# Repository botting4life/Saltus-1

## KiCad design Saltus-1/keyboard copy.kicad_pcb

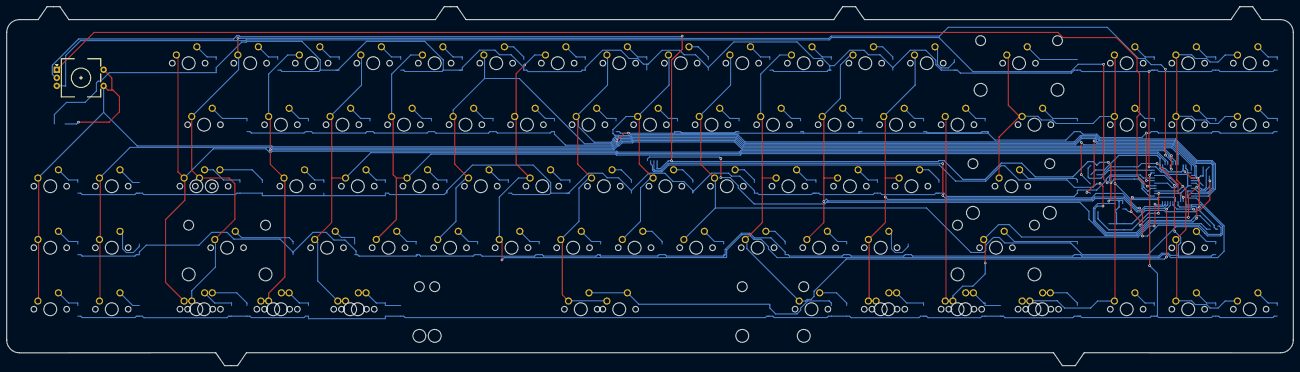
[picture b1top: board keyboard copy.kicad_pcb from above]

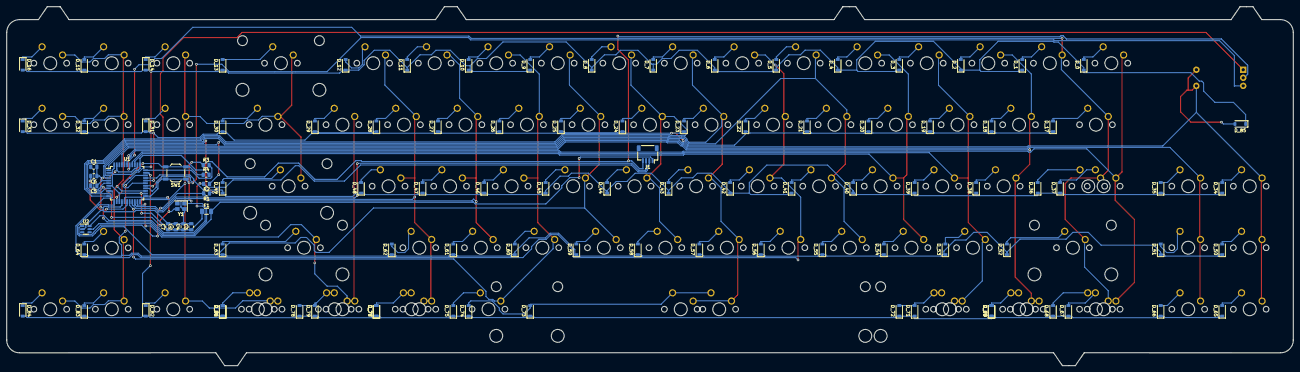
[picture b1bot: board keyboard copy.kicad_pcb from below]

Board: 2 copper layers, 398.5 x 111.2 mm, 189 parts (103 on the bottom side), 117 nets.

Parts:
C1: 1u; C_0805_2012Metric
C2, C3, C4: 0.1u; C_0805_2012Metric
C5, C6: 22p; C_0805_2012Metric
C7: 10u; C_0805_2012Metric
D_0, D_1, D_2, D_3, D_4, D_5, D_6, D_7, D_8, D_9, D_10, D_11, D_12, D_13, D_14, D_15, D_16, D_17, D_18, D_19, D_20, D_21, D_22, D_23, D_24, D_25, D_26, D_27, D_28, D_29, D_30, D_31, D_32, D_33, D_34, D_35, D_36, D_37, D_38, D_39, D_40, D_41, D_42, D_43, D_44, D_45, D_46, D_47, D_48, D_49, D_50, D_51, D_52, D_53, D_54, D_55, D_56, D_57, D_58, D_59, D_60, D_61, D_62, D_63, D_64, D_65, D_66, D_67, D_68, D_69, D_70, D_71, D_72, D_73, D_74, D_75, D_76, D_77, D_78, D_79, D_80, D_81, D_82, D_83, D_84, D_85: D; D_SOD-123
F1: 500mA; Fuse_1206_3216Metric
J1: JST SH 4-pin; JST_SH_SM04B-SRSS-TB_1x04-1MP_P1.00mm_Horizontal
K_0, K_1, K_2, K_3, K_4, K_5, K_6, K_7, K_8, K_9, K_10, K_11, K_12, K_14, K_15, K_16, K_18, K_19, K_20, K_21, K_22, K_23, K_24, K_25, K_26, K_27, K_28, K_29, K_31, K_32, K_33, K_34, K_35, K_37, K_38, K_39, K_40, K_41, K_42, K_43, K_44, K_45, K_46, K_47, K_48, K_50, K_51, K_53, K_54, K_55, K_56, K_57, K_58, K_59, K_60, K_61, K_62, K_64, K_65, K_66, K_68, K_69, K_70, K_71, K_72, K_75, K_76, K_77, K_78, K_79, K_80, K_82, K_83, K_84: KEYSW; MXOnly-1U-NoLED
K_13: KEYSW; MXOnly-2U-NoLED
K_17, K_30: KEYSW; MXOnly-1.5U-NoLED
K_36: KEYSW; MXOnly-1.75U-NoLED
K_49, K_52: KEYSW; MXOnly-2.25U-NoLED
K_63: KEYSW; MXOnly-2.75U-NoLED
K_67, K_81: KEYSW; MXOnly-1.25U-NoLED
K_73: KEYSW; MXOnly-6.25U-NoLED
K_74: KEYSW; MXOnly-7U-NoLED
R1, R2: 22; R_0805_2012Metric
R3, R4: 10k; R_0805_2012Metric
SW1: Reset; SW_SPST_TL3342
SW2: RotaryEncoder_Switch; RotaryEncoder_EC11
U1: ATmega32U4-AU; TQFP-44_10x10mm_P0.8mm
U2: SRV05-4; SOT-23-6
Y1: 16MHz; Crystal_SMD_3225-4Pin_3.2x2.5mm

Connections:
+5V: C2.1, C3.1, C4.1, C7.1, F1.1, R4.2, U1.2 (UVCC), U1.7 (VBUS), U1.14 (VCC), U1.24 (AVCC), U1.34 (VCC), U1.44 (AVCC)
/MCU_D+: R1.1, U1.4 (D+)
/MCU_D-: R2.1, U1.3 (D-)
D+: J1.3, R1.2, U2.1 (IO1)
D-: J1.2, R2.2, U2.6 (IO4)
GND: C1.2, C2.2, C3.2, C4.2, C5.1, C6.1, C7.2, J1.4, R3.1, SW1.1, SW2.C, U1.5 (UGND), U1.15 (GND), U1.23 (GND), U1.35 (GND), U1.43 (GND), U2.2 (VN), Y1.2, Y1.4
unnamed: D_0.2 (A), K_0.2 (ROW)
unnamed: D_1.2 (A), K_1.2 (ROW)
unnamed: D_2.2 (A), K_2.2 (ROW)
unnamed: D_3.2 (A), K_3.2 (ROW)
unnamed: D_4.2 (A), K_4.2 (ROW)
unnamed: D_5.2 (A), K_5.2 (ROW)
unnamed: D_6.2 (A), K_6.2 (ROW)
unnamed: D_7.2 (A), K_7.2 (ROW)
unnamed: D_8.2 (A), K_8.2 (ROW)
unnamed: D_9.2 (A), K_9.2 (ROW)
unnamed: D_10.2 (A), K_10.2 (ROW)
unnamed: D_11.2 (A), K_11.2 (ROW)
unnamed: D_12.2 (A), K_12.2 (ROW)
unnamed: D_13.2 (A), K_13.2 (ROW)
unnamed: D_14.1 (K), K_14.2 (ROW)
unnamed: D_15.2 (A), K_15.2 (ROW)
unnamed: D_16.1 (K), K_16.2 (ROW)
unnamed: D_17.2 (A), K_17.2 (ROW)
unnamed: D_18.2 (A), K_18.2 (ROW)
unnamed: D_19.2 (A), K_19.2 (ROW)
unnamed: D_20.2 (A), K_20.2 (ROW)
unnamed: D_21.2 (A), K_21.2 (ROW)
unnamed: D_22.2 (A), K_22.2 (ROW)
unnamed: D_23.2 (A), K_23.2 (ROW)
unnamed: D_24.2 (A), K_24.2 (ROW)
unnamed: D_25.2 (A), K_25.2 (ROW)
unnamed: D_26.2 (A), K_26.2 (ROW)
unnamed: D_27.2 (A), K_27.2 (ROW)
unnamed: D_28.2 (A), K_28.2 (ROW)
unnamed: D_29.2 (A), K_29.2 (ROW)
unnamed: D_30.2 (A), K_30.2 (ROW)
unnamed: D_31.1 (K), K_31.2 (ROW)
unnamed: D_32.2 (A), K_32.2 (ROW)
unnamed: D_33.1 (K), K_33.2 (ROW)
unnamed: D_34.2 (A), K_34.2 (ROW)
unnamed: D_35.2 (A), K_35.2 (ROW)
unnamed: D_36.2 (A), K_36.2 (ROW)
unnamed: D_37.2 (A), K_37.2 (ROW)
unnamed: D_38.2 (A), K_38.2 (ROW)
unnamed: D_39.2 (A), K_39.2 (ROW)
unnamed: D_40.2 (A), K_40.2 (ROW)
unnamed: D_41.2 (A), K_41.2 (ROW)
unnamed: D_42.2 (A), K_42.2 (ROW)
unnamed: D_43.2 (A), K_43.2 (ROW)
unnamed: D_44.2 (A), K_44.2 (ROW)
unnamed: D_45.2 (A), K_45.2 (ROW)
unnamed: D_46.2 (A), K_46.2 (ROW)
unnamed: D_47.2 (A), K_47.2 (ROW)
unnamed: D_48.2 (A), K_48.2 (ROW)
unnamed: D_49.2 (A), K_49.2 (ROW)
unnamed: D_50.2 (A), K_50.2 (ROW)
unnamed: D_51.2 (A), K_51.2 (ROW)
unnamed: D_52.2 (A), K_52.2 (ROW)
unnamed: D_53.2 (A), K_53.2 (ROW)
unnamed: D_54.2 (A), K_54.2 (ROW)
unnamed: D_55.2 (A), K_55.2 (ROW)
unnamed: D_56.2 (A), K_56.2 (ROW)
unnamed: D_57.2 (A), K_57.2 (ROW)
unnamed: D_58.2 (A), K_58.2 (ROW)
unnamed: D_59.2 (A), K_59.2 (ROW)
unnamed: D_60.2 (A), K_60.2 (ROW)
unnamed: D_61.2 (A), K_61.2 (ROW)
unnamed: D_62.2 (A), K_62.2 (ROW)
unnamed: D_63.2 (A), K_63.2 (ROW)
unnamed: D_64.2 (A), K_64.2 (ROW)
unnamed: D_65.2 (A), K_65.2 (ROW)
unnamed: D_66.2 (A), K_66.2 (ROW)
unnamed: D_67.2 (A), K_67.2 (ROW)
unnamed: D_68.2 (A), K_68.2 (ROW)
unnamed: D_69.2 (A), D_70.2 (A), K_69.2 (ROW), K_70.2 (ROW)
unnamed: D_71.2 (A), D_72.2 (A), K_71.2 (ROW), K_72.2 (ROW)
unnamed: D_73.2 (A), D_74.2 (A), K_73.2 (ROW), K_74.2 (ROW)
unnamed: D_75.2 (A), K_75.2 (ROW)
unnamed: D_76.2 (A), D_77.2 (A), K_76.2 (ROW), K_77.2 (ROW)
unnamed: D_78.2 (A), D_79.2 (A), K_78.2 (ROW), K_79.2 (ROW)
unnamed: D_80.2 (A), D_81.2 (A), K_80.2 (ROW), K_81.2 (ROW)
unnamed: D_82.1 (K), K_82.2 (ROW)
unnamed: D_83.2 (A), K_83.2 (ROW)
unnamed: D_84.1 (K), K_84.2 (ROW)
unnamed: D_85.2 (A), SW2.S2
unnamed: C1.1, U1.6 (UCAP)
unnamed: R3.2, U1.33 (~HWB/PE2)
RST: R4.1, SW1.2, U1.13 (~RESET)
VBUS: F1.2, J1.1, U2.5 (VP)
XTAL1: C6.2, U1.17 (XTAL1), Y1.1
XTAL2: C5.2, U1.16 (XTAL2), Y1.3
col0: K_34.1 (COL), K_50.1 (COL), K_65.1 (COL), SW2.S1, U1.1 (PE6)
col1: K_35.1 (COL), K_51.1 (COL), K_66.1 (COL), U1.41 (PF0)
col2: K_0.1 (COL), K_37.1 (COL), K_67.1 (COL), U1.40 (PF1)
col3: K_1.1 (COL), K_17.1 (COL), K_36.1 (COL), K_52.1 (COL), K_68.1 (COL), U1.39 (PF4)
col4: K_2.1 (COL), K_18.1 (COL), K_38.1 (COL), K_69.1 (COL), K_70.1 (COL), U1.38 (PF5)
col5: K_3.1 (COL), K_19.1 (COL), K_39.1 (COL), K_53.1 (COL), K_71.1 (COL), K_72.1 (COL), U1.37 (PF6)
col6: K_4.1 (COL), K_20.1 (COL), K_40.1 (COL), K_54.1 (COL), U1.36 (PF7)
col7: K_5.1 (COL), K_21.1 (COL), K_41.1 (COL), K_55.1 (COL), U1.8 (PB0)
col8: K_6.1 (COL), K_22.1 (COL), K_42.1 (COL), K_56.1 (COL), U1.9 (PB1)
col9: K_7.1 (COL), K_23.1 (COL), K_43.1 (COL), K_57.1 (COL), K_73.1 (COL), K_74.1 (COL), U1.10 (PB2)
col10: K_8.1 (COL), K_24.1 (COL), K_44.1 (COL), K_58.1 (COL), U1.11 (PB3)
col11: K_9.1 (COL), K_25.1 (COL), K_45.1 (COL), K_59.1 (COL), U1.12 (PB7)
col12: K_10.1 (COL), K_26.1 (COL), K_46.1 (COL), K_60.1 (COL), K_75.1 (COL), U1.18 (PD0)
col13: K_11.1 (COL), K_27.1 (COL), K_47.1 (COL), K_61.1 (COL), U1.19 (PD1)
col14: K_12.1 (COL), K_28.1 (COL), K_48.1 (COL), K_62.1 (COL), K_76.1 (COL), K_77.1 (COL), U1.20 (PD2)
col15: K_29.1 (COL), K_63.1 (COL), K_78.1 (COL), K_79.1 (COL), U1.21 (PD3)
col16: K_13.1 (COL), K_14.1 (COL), K_30.1 (COL), K_31.1 (COL), K_49.1 (COL), K_80.1 (COL), K_81.1 (COL), K_82.1 (COL), U1.22 (PD5)
col17: K_15.1 (COL), K_16.1 (COL), K_32.1 (COL), K_33.1 (COL), K_64.1 (COL), K_83.1 (COL), K_84.1 (COL), U1.25 (PD4)
encA: SW2.B, U1.26 (PD6)
encB: SW2.A, U1.27 (PD7)
link2: D_0.1 (K), D_1.1 (K), D_2.1 (K), D_3.1 (K), D_4.1 (K), D_5.1 (K), D_6.1 (K), D_7.1 (K), D_8.1 (K), D_9.1 (K), D_10.1 (K), D_11.1 (K), D_12.1 (K), D_13.1 (K), D_14.2 (A), D_15.1 (K), D_16.2 (A), D_85.1 (K), U1.28 (PB4)
row1: D_17.1 (K), D_18.1 (K), D_19.1 (K), D_20.1 (K), D_21.1 (K), D_22.1 (K), D_23.1 (K), D_24.1 (K), D_25.1 (K), D_26.1 (K), D_27.1 (K), D_28.1 (K), D_29.1 (K), D_30.1 (K), D_31.2 (A), D_32.1 (K), D_33.2 (A), U1.29 (PB5)
row2: D_34.1 (K), D_35.1 (K), D_36.1 (K), D_37.1 (K), D_38.1 (K), D_39.1 (K), D_40.1 (K), D_41.1 (K), D_42.1 (K), D_43.1 (K), D_44.1 (K), D_45.1 (K), D_46.1 (K), D_47.1 (K), D_48.1 (K), D_49.1 (K), U1.30 (PB6)
row3: D_50.1 (K), D_51.1 (K), D_52.1 (K), D_53.1 (K), D_54.1 (K), D_55.1 (K), D_56.1 (K), D_57.1 (K), D_58.1 (K), D_59.1 (K), D_60.1 (K), D_61.1 (K), D_62.1 (K), D_63.1 (K), D_64.1 (K), U1.31 (PC6)
row4: D_65.1 (K), D_66.1 (K), D_67.1 (K), D_68.1 (K), D_69.1 (K), D_70.1 (K), D_71.1 (K), D_72.1 (K), D_73.1 (K), D_74.1 (K), D_75.1 (K), D_76.1 (K), D_77.1 (K), D_78.1 (K), D_79.1 (K), D_80.1 (K), D_81.1 (K), D_82.2 (A), D_83.1 (K), D_84.2 (A), U1.32 (PC7)
